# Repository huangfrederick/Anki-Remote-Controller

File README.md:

# Antimicrobial, Remineralizing Dental Composites

Simple wireless controller for reviewing anki decks. It's just 5 buttons to navigate the desktop UI.

Header file for bluetooth communications were obtained through open source software. Probably wasn't worth the time troubleshooting something written myself if there was already an existing platform for it. See uploaded 'ESP32-BLE-Keyboard' folder for details about the header file code.

Written for esp32 development boards.

Designs were drafted in KiCAD and production was outsourced to JLCPCB. Manufacturing settings can be found from their website.

Rest of the files are ones required by the manufacturer to produce the board.

## Description

### Why This Matters

Med students really like Anki for flashcards. Why do flashcards while sitting at a computer when you can do it from afar simultaneously with other tasks? 

### What This Aims to Achieve

Transmit button inputs as keystrokes to a personal computer.

## Getting Started

* Nothing really here. This is mainly for documentation. You can download the associated scripts used for sending and receiving data from the remote to a computer.
* If you want to make your own remote, you will need 1) any eCAD software, 2) ESP32 development board, and 3) female to male jumper wires with a battery bank or some way to power the board.

### Dependencies

* Again, nothing much here.
* If you want to replicate the workflow here, this'll require an active version of C++, an IDE of your choice, and libraries that are found within the uploaded files.

### Installing

* See uploaded files.

### Executing program

* Upload script to development board through an IDE like VSCode.

## Authors

Frederick Huang

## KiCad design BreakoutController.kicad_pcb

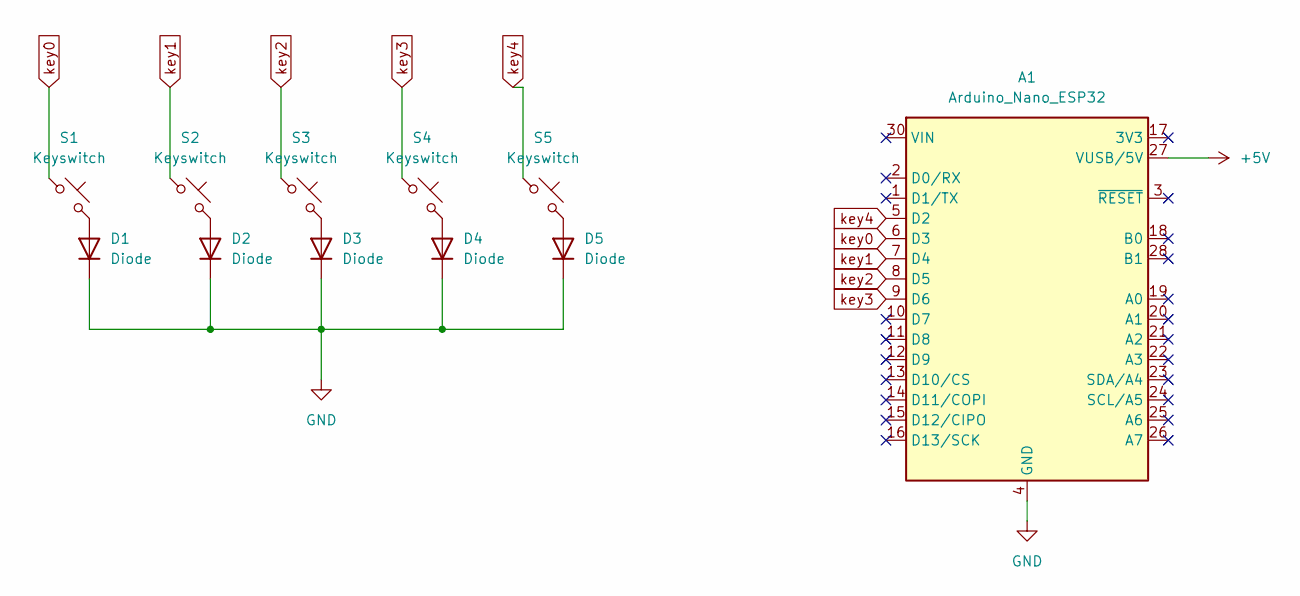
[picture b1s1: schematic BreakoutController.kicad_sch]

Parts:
A1: Arduino_Nano_ESP32; Arduino_Nano
D1, D2, D3, D4, D5: Diode; D_SOD-123
S1, S2, S3, S4, S5: Keyswitch; MX-Hotswap-1U

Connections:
+5V: A1.27 (VUSB/5V)
GND: A1.4 (GND), A1.29 (GND), D1.1 (K), D2.1 (K), D3.1 (K), D4.1 (K), D5.1 (K)
unnamed: D1.2 (A), S1.2
unnamed: D2.2 (A), S2.2
unnamed: D3.2 (A), S3.2
unnamed: D4.2 (A), S4.2
unnamed: D5.2 (A), S5.2
key0: A1.6 (D3), S1.1
key1: A1.7 (D4), S2.1
key2: A1.8 (D5), S3.1
key3: A1.9 (D6), S4.1
key4: A1.5 (D2), S5.1

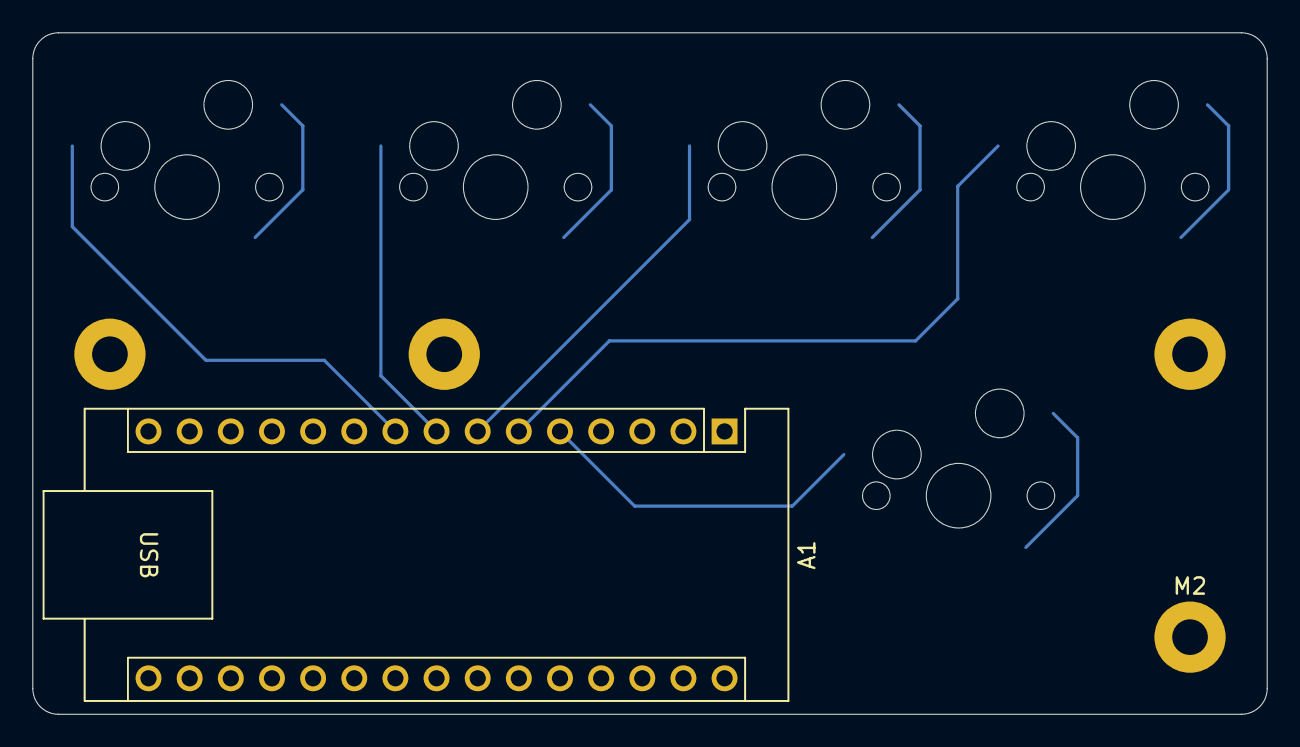
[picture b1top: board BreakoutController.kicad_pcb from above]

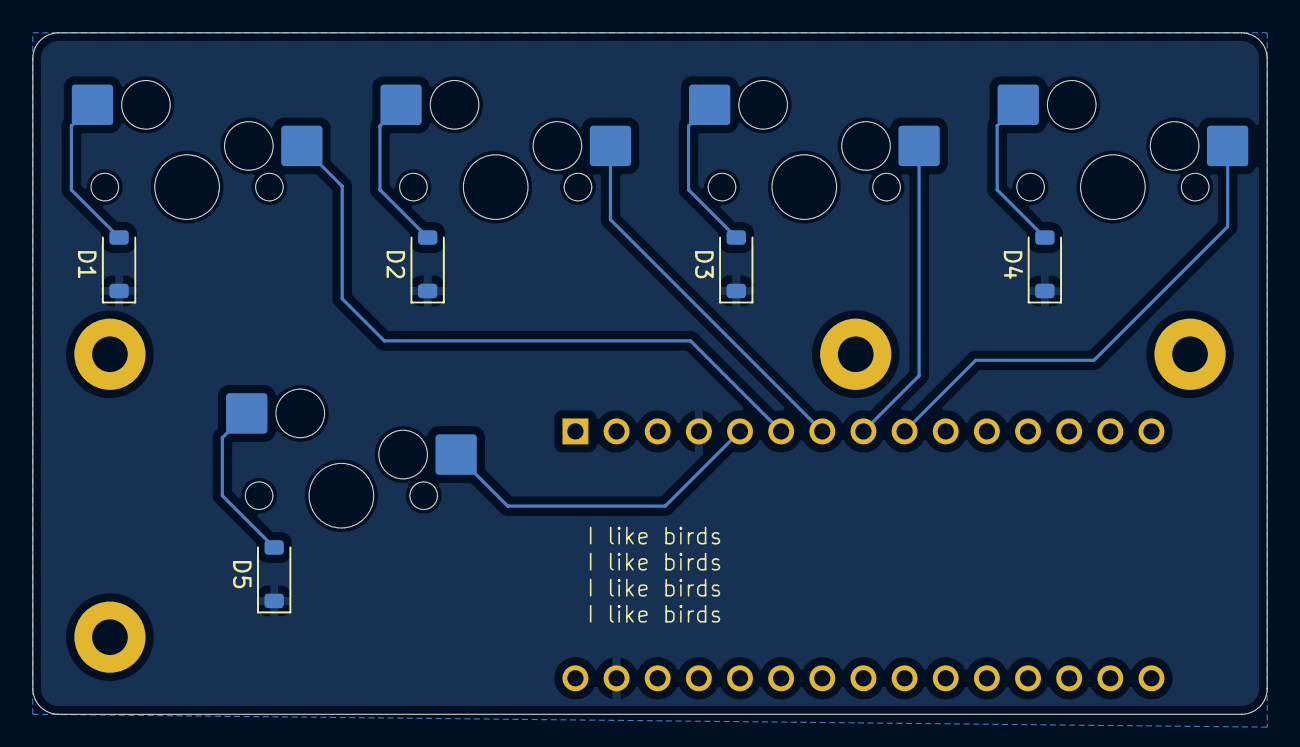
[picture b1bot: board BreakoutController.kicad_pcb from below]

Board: 2 copper layers, 76.2 x 42.1 mm, 12 parts (10 on the bottom side), 11 nets.

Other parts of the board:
M2: M2 Pad; MountingHole_2.2mm_M2_Pad

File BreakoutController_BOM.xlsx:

Comment | Designator | Footprint | JLCPCB Part #（optional）
SMD diode | D1 | Diode_SMD:D_SOD-123 | C2972760
SMD diode | D2 | Diode_SMD:D_SOD-123 | C2972760
SMD diode | D3 | Diode_SMD:D_SOD-123 | C2972760
SMD diode | D4 | Diode_SMD:D_SOD-123 | C2972760
SMD diode | D5 | Diode_SMD:D_SOD-123 | C2972760
SMD switch socket | S1 | SMD,14.5x5.9mm | C41430893
SMD switch socket | S2 | SMD,14.5x5.9mm | C41430893
SMD switch socket | S3 | SMD,14.5x5.9mm | C41430893
SMD switch socket | S4 | SMD,14.5x5.9mm | C41430893
SMD switch socket | S5 | SMD,14.5x5.9mm | C41430893

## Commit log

2026-04-14 Added Production Files
